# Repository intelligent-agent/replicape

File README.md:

:::python
     _____           __
    | ___ \         | (_)
    | |_/ /___ _ __ | |_  ___ __ _ _ __   ___
    |    // _ \  _ \| | |/ __/ _  |  _ \ / _ \
    | |\ \  __/ |_) | | | (_| (_| | |_) |  __/
    \_| \_\___| .__/|_|_|\___\__,_| .__/ \___|
             | |                 | |
             |_|                 |_|

Replicape is a 3D printer cape for BeagleBone.  

### Features: ###

* 5 stepper motors (Trinamic TMC2100) (X, Y, Z, E, H)  
* 3 high power MOSFETs (PWM controlled) for 2 extruders and 1 HPB.  (12..24V)  
* 4 medium power MOSFETs (PWM controlled) for up to 4 fans/LED strips.  (12V)  
* 3 analog input ports for thermistors. noise-filtered inputs and option for shielding  
* 6 inputs for end stops (X, Y, Z).  
* 1 bus for Dallas 1W temperature sensor for monitoring the cold end. Up to 10 sensors can be added to the bus.  
* 2 servo outputs.  
* 1 inductive sensor input.  
* Programmable current limits on steppers motor drivers (SMD). No need to manually adjust a pot meter.  
* Microstepping individually programmable for each SMD from 1 to 256.  
* All steppers are controlled by the Programmable Realtime Unit (PRU) for hard real time operation.  
* Compatible with [Manga Screen](https://bitbucket.org/intelligentagent/manga-screen)  
* Single 12 to 24V PSU, fans are still 12V.  
* Compatible with BeagleBone and BeagleBone Black (probably also green and blue).  
* Open source hardware and software. (CC BY-SA)  
* Software written in Python for maintainability and hackability.  
  
This is the repository for the hardware, the "firmware" (Redeem) has a [separate repository](https://bitbucket.org/intelligentagent/redeem)

### What is in here? ###

* This repository contains the files needed to reproduce the PCB and continue development.
* The latest revision is B3

### I want one! How much is it, and where can I get it? ###

It's $99 and you can [buy it in the store](http://www.thing-printer.com/product/replicape)

### I want to build my own board. How do I do that? ###

* Download the BOM and order the parts from Digi-key
* Send the GERBER files to a PCB manufacturer
* Get a reflow oven
* Populate the board

### I want a different version of this, who do I talk to? ###

Talk to Elias <elias at iagent dot no> 

### I have a Replicape, how do I wire it? ###
Look at the wiki page: [http://wiki.thing-printer.com](http://wiki.thing-printer.com)

### I want to read about the latest development of this board. Where can I do that? ###
The thing-prnter blog is a good place: [http://www.thing-printer.com/blog/](http://www.thing-printer.com/blog/)

### Who has contributed to this project? ###

* Elias Bakken
* Dirk Eichel
* Stoneshop
* Bent Furevik

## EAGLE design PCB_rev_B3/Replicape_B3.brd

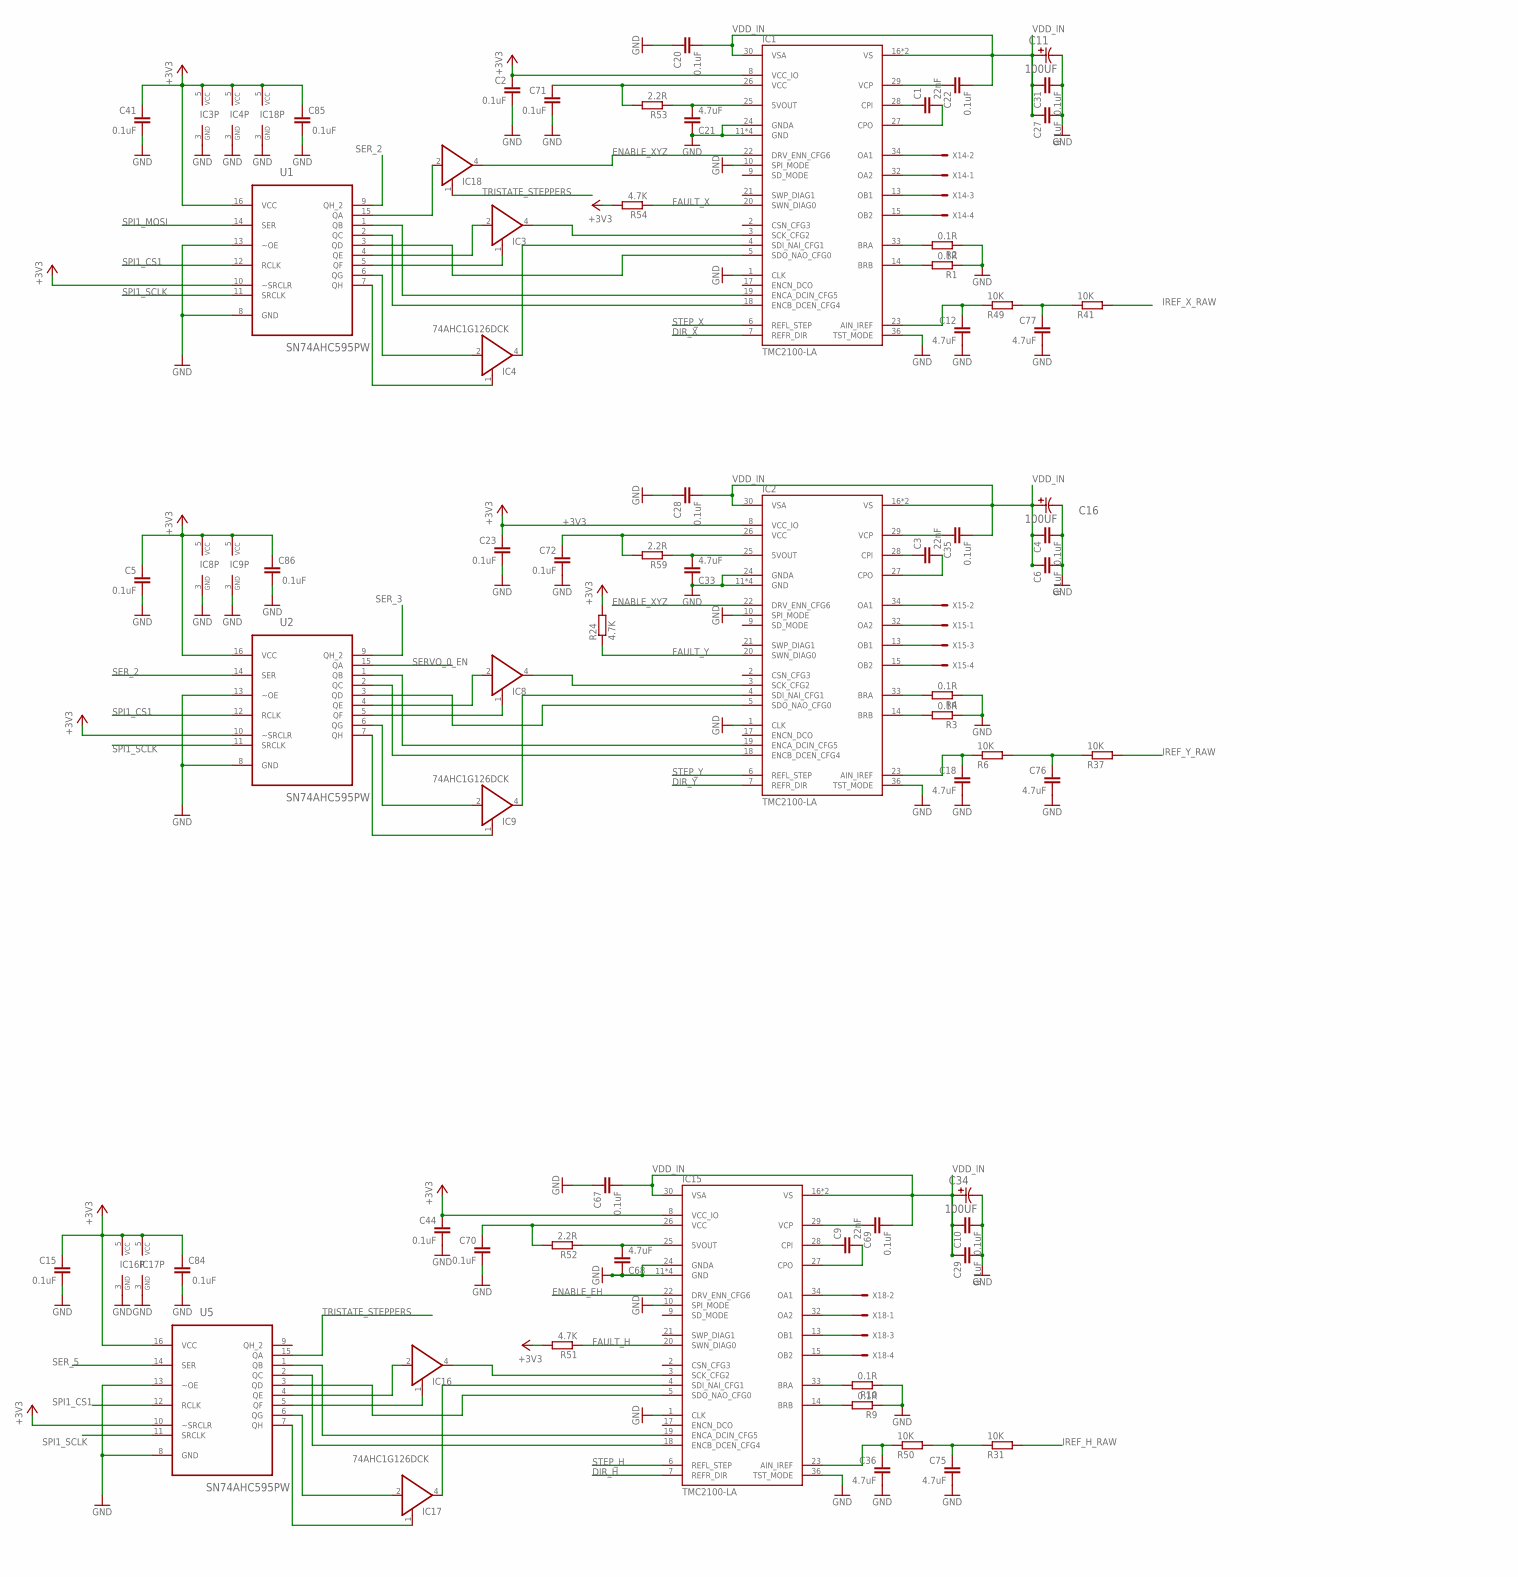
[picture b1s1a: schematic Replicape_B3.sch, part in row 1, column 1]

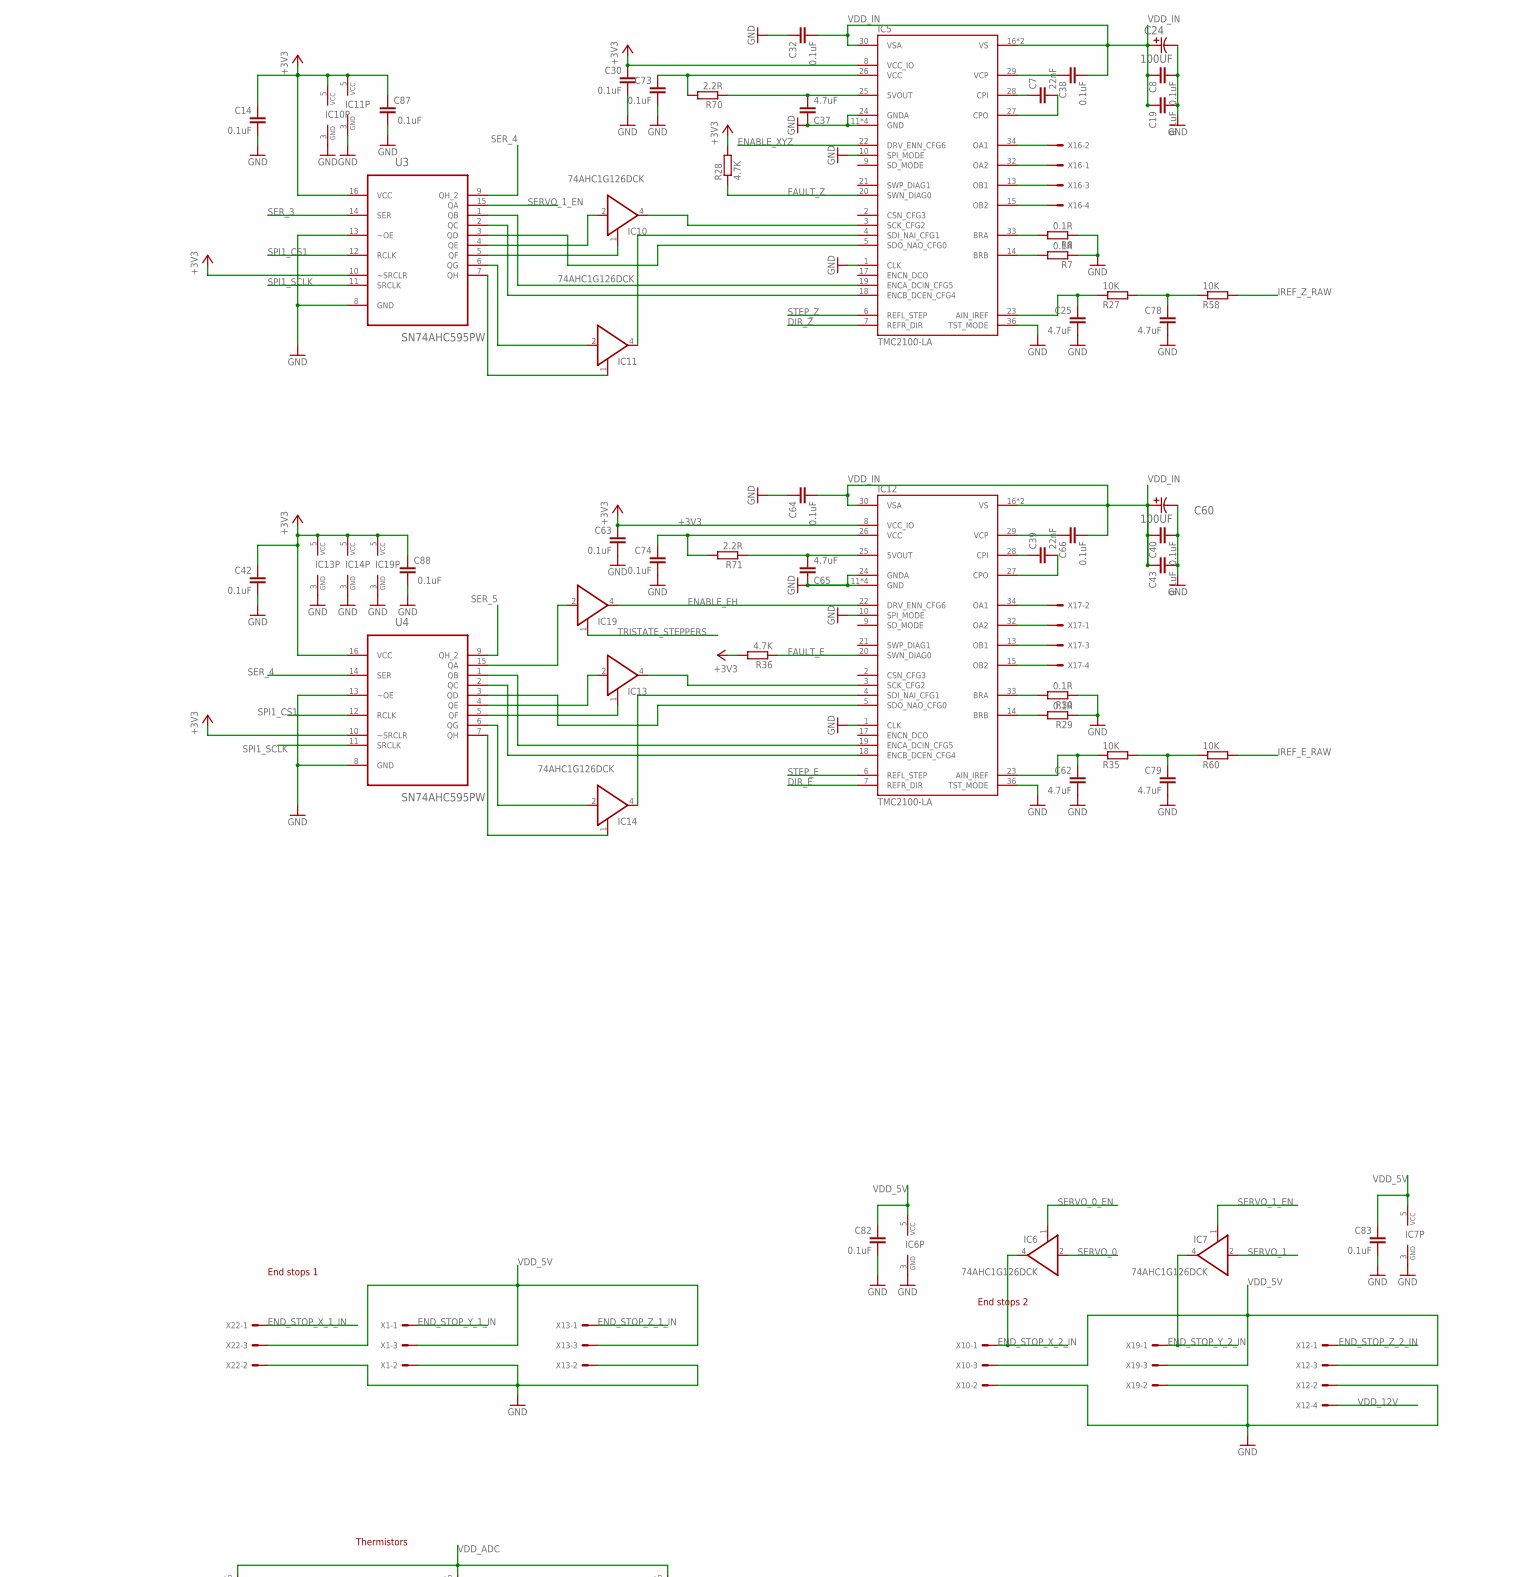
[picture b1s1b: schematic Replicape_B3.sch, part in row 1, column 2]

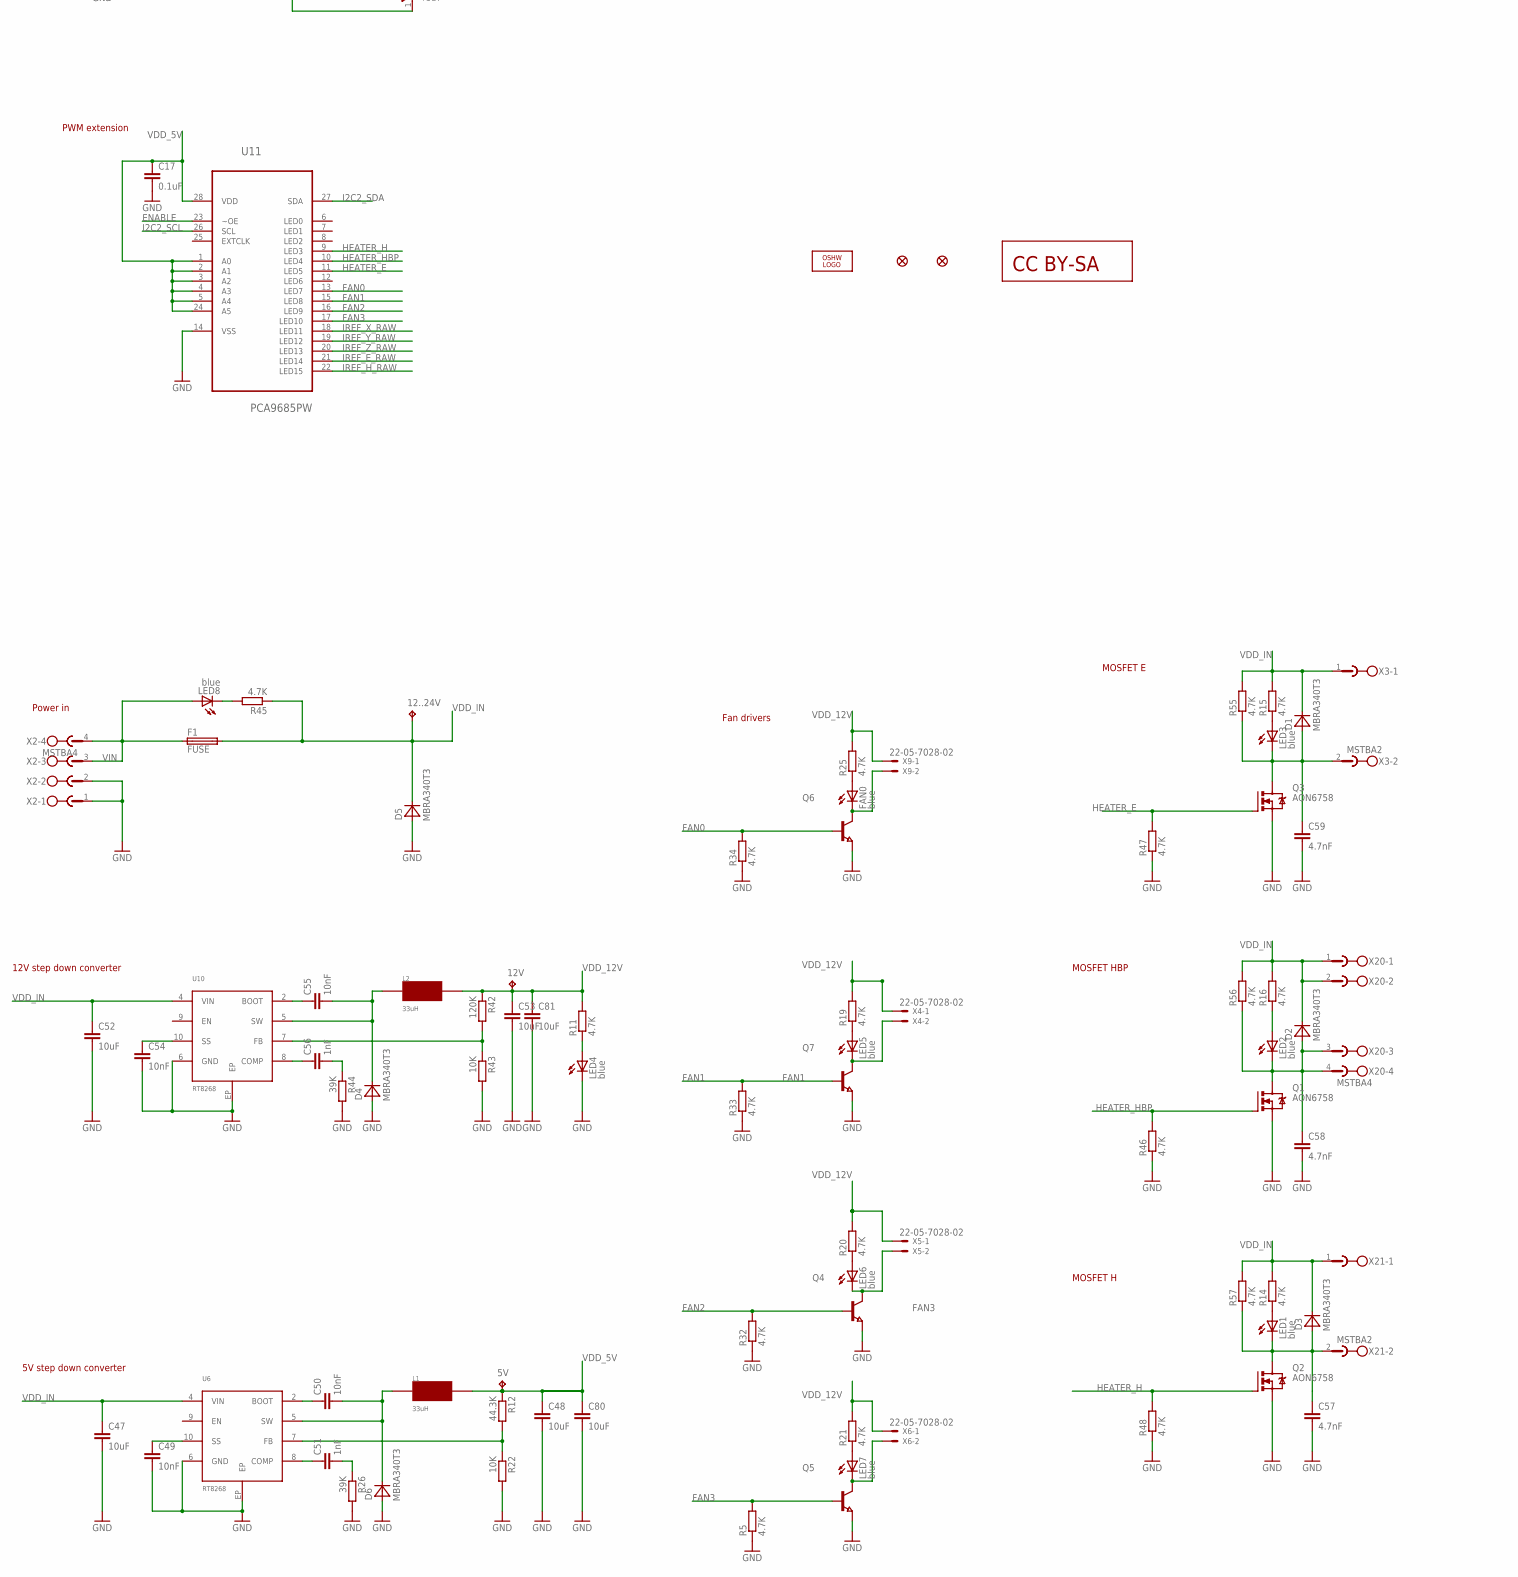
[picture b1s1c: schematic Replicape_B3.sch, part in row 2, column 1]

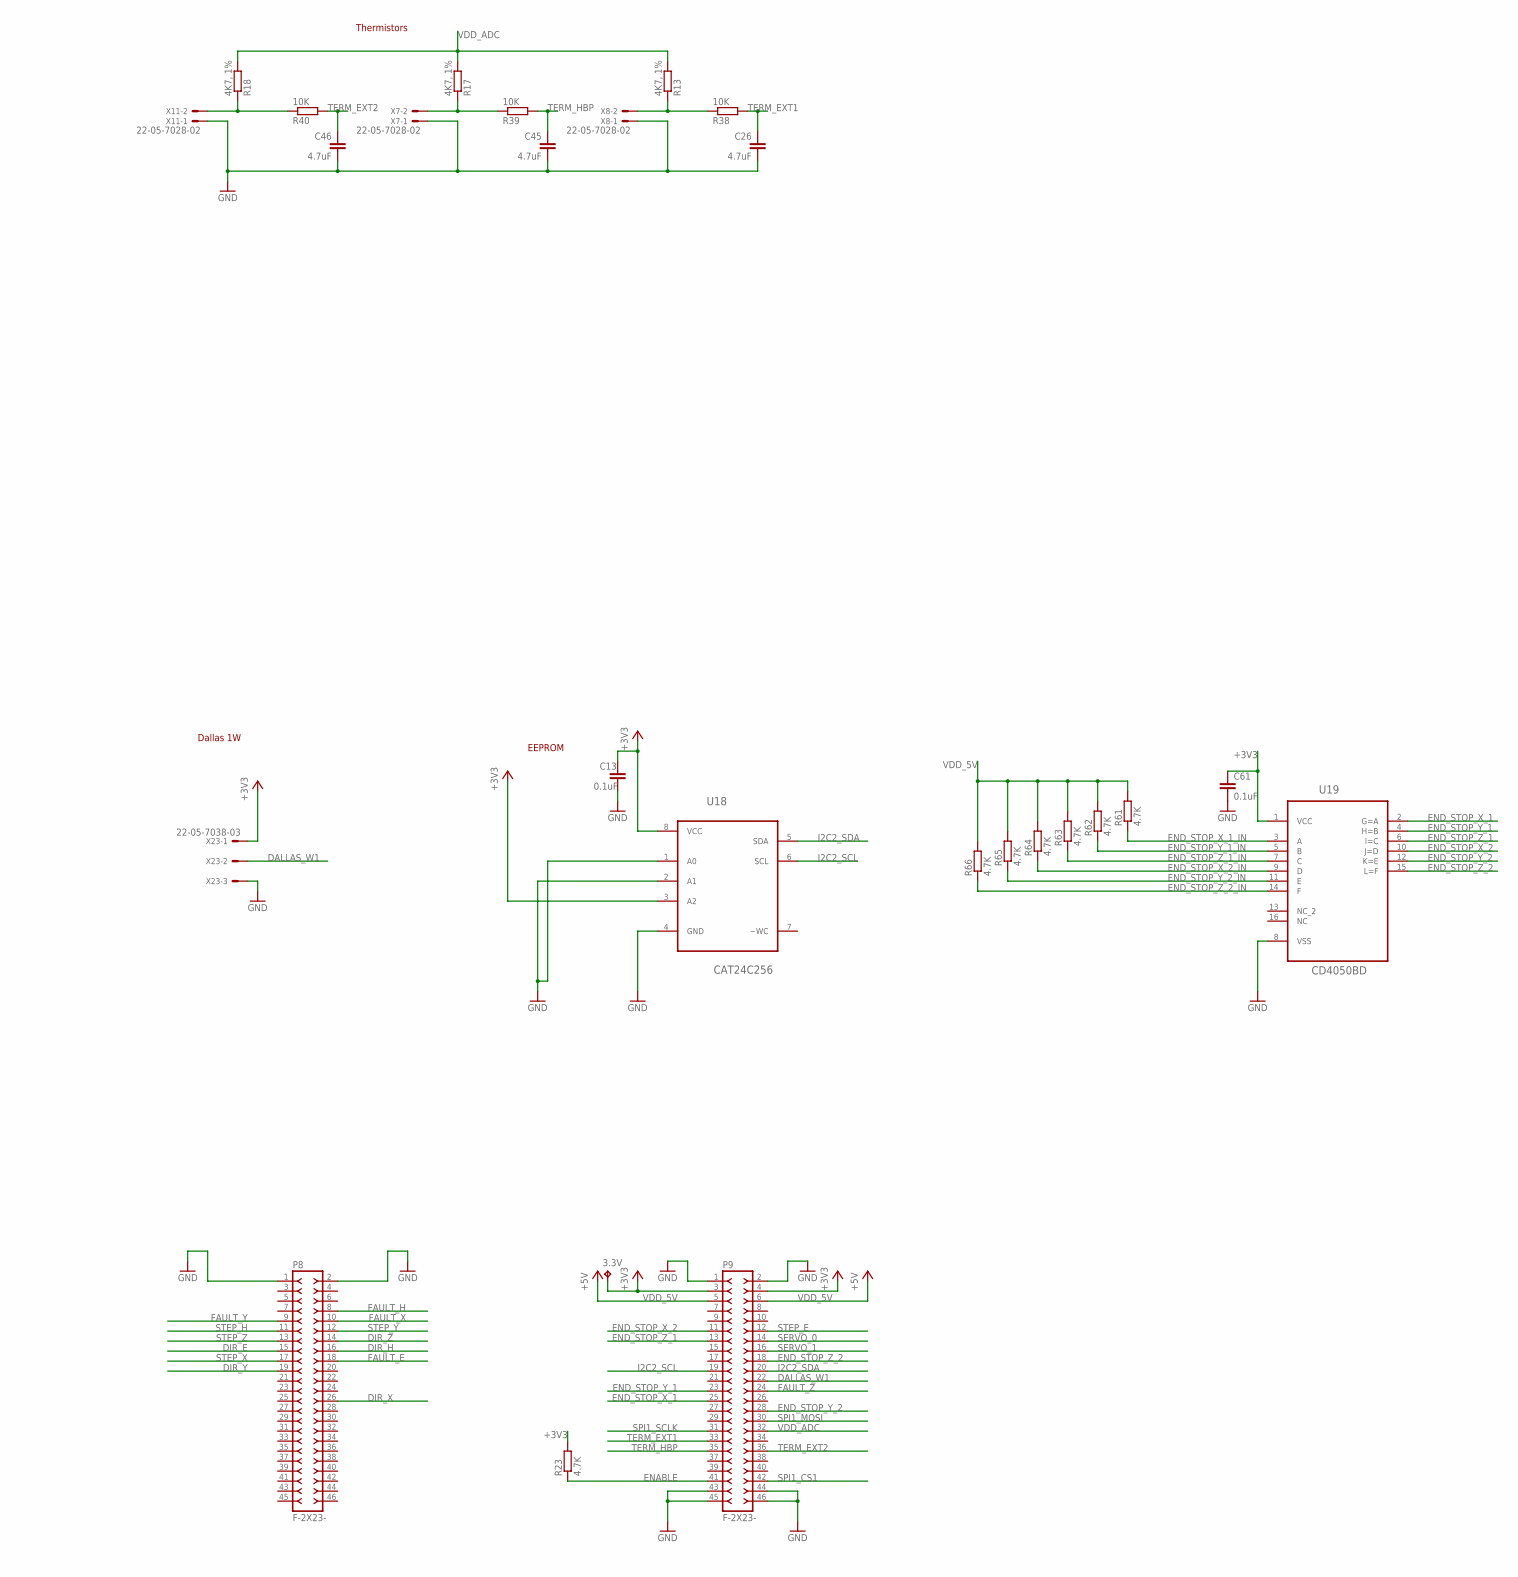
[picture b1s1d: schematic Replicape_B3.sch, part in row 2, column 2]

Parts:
3.3V, 5V, 12..24V, 12V: TPB1,27; B1,27
C1, C3, C7, C9, C39: 22nF; C0402
C2, C4, C5, C6, C8, C10, C13, C14, C15, C17, C19, C20, C22, C23, C27, C28, C29, C30, C31, C32, C35, C38, C40, C41, C42, C43, C44, C61, C63, C64, C66, C67, C69, C70, C71, C72, C73, C74, C82, C83, C84, C85, C86, C87, C88: 0.1uF; C0402
C11, C16, C24, C34, C60: 100UF; CAPAE660X800N
C12, C18, C21, C25, C26, C33, C36, C37, C45, C46, C62, C65, C68, C75, C76, C77, C78, C79: 4.7uF; C0402
C47, C48, C52, C53, C80, C81: 10uF; C1206
C49, C50, C54, C55: 10nF; C0402
C51, C56: 1nF; C0402
C57, C58, C59: 4.7nF; C0402
D1, D2, D3, D4, D5, D6: MBRA340T3; SMA
F1: FUSE; 3557
FAN0: blue; CHIP-LED0603
IC1, IC2, IC5, IC12, IC15: TMC2100-LA; QFN36-PAD
IC3, IC4, IC6, IC7, IC8, IC9, IC10, IC11, IC13, IC14, IC16, IC17, IC18, IC19: 74AHC1G126DCK; SC70-5
JP1, JP2: FIDUCIAL1X2.5; FIDUCIAL-1X2.5
L1, L2: 33uH; NR8040T330
LED1, LED2, LED3, LED4, LED5, LED6, LED7, LED8: blue; CHIP-LED0603
LOGO1: OSHW_LOGO_FILLX0200-NT; OSHW_FILLX200_NOTEXT
P8, P9: F-2X23-; DIL-100-2X23
Q1, Q2, Q3: AON6758; 8-DFN-EP-(5X6)
Q4, Q5, Q6, Q7: NPN-TRANSISTOR_SOT23; SOT23
R1, R2, R3, R4, R7, R8, R9, R10, R29, R30: 0.1R; R0805
R5, R11, R14, R15, R16, R19, R20, R21, R23, R24, R25, R28, R32, R33, R34, R36, R45, R46, R47, R48, R51, R54, R55, R56, R57, R61, R62, R63, R64, R65, R66: 4.7K; R0402
R6, R22, R27, R31, R35, R37, R38, R39, R40, R41, R43, R49, R50, R58, R60: 10K; R0402
R12: 44.3K; R0402
R13, R17, R18: 4K7, 1%; R0402
R26, R44: 39K; R0402
R42: 120K; R0402
R52, R53, R59, R70, R71: 2.2R; R0402
U1, U2, U3, U4, U5: SN74AHC595PW; SOP65P640X120-16N
U6, U10: RT8268; MSOP10
U11: PCA9685PW; SOP65P640X110-28N
U18: CAT24C256; SOIC127P600X175-8N
U19: CD4050BD; SOIC127P600X175-16N
U$4: CC-BY-SA
X1, X10, X13, X19, X22, X23: 22-05-7038-03; 7395-03
X2, X20: MSTBA4
X3, X21: MSTBA2
X4, X5, X6, X7, X8, X9, X11: 22-05-7028-02; 7395-02
X12, X14, X15, X16, X17, X18: 22-05-7048-04; 7395-04

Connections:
+3V3: 3.3V.TP, C2.1, C5.1, C13.1, C14.1, C15.1, C23.1, C30.1, C41.1, C42.1, C44.1, C61.1, C63.1, C84.1, C85.1, C86.1, C87.1, C88.1, IC1.8 (VCC_IO), IC2.8 (VCC_IO), IC3.5 (VCC), IC4.5 (VCC), IC5.8 (VCC_IO), IC8.5 (VCC), IC9.5 (VCC), IC10.5 (VCC), IC11.5 (VCC), IC12.8 (VCC_IO), IC13.5 (VCC), IC14.5 (VCC), IC15.8 (VCC_IO), IC16.5 (VCC), IC17.5 (VCC), IC18.5 (VCC), IC19.5 (VCC), P9.3, P9.4, R23.2, R24.2, R28.2, R36.2, R51.2, R54.2, U1.10 (~SRCLR), U1.16 (VCC), U2.10 (~SRCLR), U2.16 (VCC), U3.10 (~SRCLR), U3.16 (VCC), U4.10 (~SRCLR), U4.16 (VCC), U5.10 (~SRCLR), U5.16 (VCC), U18.3 (A2), U18.8 (VCC), U19.1 (VCC), X23.1
DALLAS_W1: P9.22, X23.2
DIR_E: IC12.7 (REFR_DIR), P8.15
DIR_H: IC15.7 (REFR_DIR), P8.16
DIR_X: IC1.7 (REFR_DIR), P8.26
DIR_Y: IC2.7 (REFR_DIR), P8.19
DIR_Z: IC5.7 (REFR_DIR), P8.14
ENABLE: P9.41, R23.1, U11.23 (~OE)
ENABLE_EH: IC12.22 (DRV_ENN_CFG6), IC15.22 (DRV_ENN_CFG6), IC19.4 (O)
ENABLE_XYZ: IC1.22 (DRV_ENN_CFG6), IC2.22 (DRV_ENN_CFG6), IC5.22 (DRV_ENN_CFG6), IC18.4 (O)
END_STOP_X_1: P9.25, U19.2 (G=A)
END_STOP_X_1_IN: R61.1, U19.3 (A), X22.1
END_STOP_X_2: P9.11, U19.10 (J=D)
END_STOP_X_2_IN: IC6.4 (O), R64.1, U19.9 (D), X10.1
END_STOP_Y_1: P9.23, U19.4 (H=B)
END_STOP_Y_1_IN: R62.1, U19.5 (B), X1.1
END_STOP_Y_2: P9.28, U19.12 (K=E)
END_STOP_Y_2_IN: IC7.4 (O), R65.1, U19.11 (E), X19.1
END_STOP_Z_1: P9.13, U19.6 (I=C)
END_STOP_Z_1_IN: R63.1, U19.7 (C), X13.1
END_STOP_Z_2: P9.18, U19.15 (L=F)
END_STOP_Z_2_IN: R66.1, U19.14 (F), X12.1
FAN0: Q6.1 (B), R34.2, U11.13 (LED7)
FAN1: Q7.1 (B), R33.2, U11.15 (LED8)
FAN2: Q4.1 (B), R32.2, U11.16 (LED9)
FAN3: Q5.1 (B), R5.2, U11.17 (LED10)
FAULT_E: IC12.20 (SWN_DIAG0), P8.18, R36.1
FAULT_H: IC15.20 (SWN_DIAG0), P8.8, R51.1
FAULT_X: IC1.20 (SWN_DIAG0), P8.10, R54.1
FAULT_Y: IC2.20 (SWN_DIAG0), P8.9, R24.1
FAULT_Z: IC5.20 (SWN_DIAG0), P9.24, R28.1
GND: C2.2, C4.2, C5.2, C6.2, C8.2, C10.2, C11.2, C12.2, C13.2, C14.2, C15.2, C16.2, C17.2, C18.2, C19.2, C20.1, C21.1, C23.2, C24.2, C25.2, C26.2, C27.2, C28.1, C29.2, C30.2, C31.2, C32.1, C33.1, C34.2, C36.2, C37.1, C40.2, C41.2, C42.2, C43.2, C44.2, C45.2, C46.2, C47.2, C48.2, C49.2, C52.2, C53.2, C54.2, C57.2, C58.2, C59.2, C60.2, C61.2, C62.2, C63.2, C64.1, C65.1, C67.1, C68.1, C70.2, C71.2, C72.2, C73.2, C74.2, C75.2, C76.2, C77.2, C78.2, C79.2, C80.2, C81.2, C82.2, C83.2, C84.2, C85.2, C86.2, C87.2, C88.2, D4.A, D5.A, D6.A, IC1.1 (CLK), IC1.10 (SPI_MODE), IC1.11 (GND), IC1.12 (GND), IC1.24 (GNDA), IC1.35 (GND), IC1.36 (TST_MODE), IC1.TP (GND), IC2.1 (CLK), IC2.10 (SPI_MODE), IC2.11 (GND), IC2.12 (GND), IC2.24 (GNDA), IC2.35 (GND), IC2.36 (TST_MODE), IC2.TP (GND), IC3.3 (GND), IC4.3 (GND), IC5.1 (CLK), IC5.10 (SPI_MODE), IC5.11 (GND), IC5.12 (GND), IC5.24 (GNDA), IC5.35 (GND), IC5.36 (TST_MODE), IC5.TP (GND), IC6.3 (GND), IC7.3 (GND), IC8.3 (GND), IC9.3 (GND), IC10.3 (GND), IC11.3 (GND), IC12.1 (CLK), IC12.10 (SPI_MODE), IC12.11 (GND), IC12.12 (GND), IC12.24 (GNDA), IC12.35 (GND), IC12.36 (TST_MODE), IC12.TP (GND), IC13.3 (GND), IC14.3 (GND), IC15.1 (CLK), IC15.10 (SPI_MODE), IC15.11 (GND), IC15.12 (GND), IC15.24 (GNDA), IC15.35 (GND), IC15.36 (TST_MODE), IC15.TP (GND), IC16.3 (GND), IC17.3 (GND), IC18.3 (GND), IC19.3 (GND), LED4.C, P8.1, P8.2, P9.1, P9.2, P9.43, P9.44, P9.45, P9.46, Q1.1 (S), Q1.2 (S), Q1.3 (S), Q2.1 (S), Q2.2 (S), Q2.3 (S), Q3.1 (S), Q3.2 (S), Q3.3 (S), Q4.2 (E), Q5.2 (E), Q6.2 (E), Q7.2 (E), R1.1, R2.1, R3.1, R4.1, R5.1, R7.1, R8.1, R9.1, R10.1, R22.2, R26.2, R29.1, R30.1, R32.1, R33.1, R34.1, R43.2, R44.2, R46.1, R47.1, R48.1, U1.8 (GND), U1.13 (~OE), U2.8 (GND), U2.13 (~OE), U3.8 (GND), U3.13 (~OE), U4.8 (GND), U4.13 (~OE), U5.8 (GND), U5.13 (~OE), U6.6 (GND), U6.EP, U10.6 (GND), U10.EP, U11.14 (VSS), U18.1 (A0), U18.2 (A1), U18.4 (GND), U19.8 (VSS), X1.2, X2.1, X2.2, X7.1, X8.1, X10.2, X11.1, X12.2, X13.2, X19.2, X22.2, X23.3
HEATER_E: Q3.4 (G), R47.2, U11.11 (LED5)
HEATER_H: Q2.4 (G), R48.2, U11.9 (LED3)
HEATER_HBP: Q1.4 (G), R46.2, U11.10 (LED4)
I2C2_SCL: P9.19, U11.26 (SCL), U18.6 (SCL)
I2C2_SDA: P9.20, U11.27 (SDA), U18.5 (SDA)
IREF_E: C79.1, R35.2, R60.1
IREF_E_RAW: R60.2, U11.21 (LED14)
IREF_H: C75.1, R31.1, R50.2
IREF_H_RAW: R31.2, U11.22 (LED15)
IREF_X: C77.1, R41.1, R49.2
IREF_X_RAW: R41.2, U11.18 (LED11)
IREF_Y: C76.1, R6.2, R37.1
IREF_Y_RAW: R37.2, U11.19 (LED12)
IREF_Z: C78.1, R27.2, R58.1
IREF_Z_RAW: R58.2, U11.20 (LED13)
unnamed: IC2.13 (OB1), X15.3
unnamed: C3.2, IC2.27 (CPO)
unnamed: IC4.1 (OE), U1.7 (QH)
unnamed: IC4.2 (I), U1.6 (QG)
unnamed: IC1.18 (ENCB_DCEN_CFG4), U1.2 (QC)
unnamed: LED8.C, R45.2
unnamed: LED5.A, R19.1
unnamed: FAN0.C, Q6.3 (C), X9.2
unnamed: C9.2, IC15.27 (CPO)
unnamed: IC15.14 (BRB), R9.2
unnamed: C7.2, IC5.27 (CPO)
unnamed: IC5.14 (BRB), R7.2
unnamed: C1.1, IC1.28 (CPI)
unnamed: C1.2, IC1.27 (CPO)
unnamed: IC1.14 (BRB), R1.2
unnamed: IC1.33 (BRA), R2.2
unnamed: C12.1, IC1.23 (AIN_IREF), R49.1
unnamed: FAN0.A, R25.1
unnamed: IC2.32 (OA2), X15.1
unnamed: R12.2, R22.1, U6.7 (FB)
unnamed: IC5.33 (BRA), R8.2
unnamed: C50.2, D6.C, L1.P$2, U6.5 (SW)
unnamed: C25.1, IC5.23 (AIN_IREF), R27.1
unnamed: C7.1, IC5.28 (CPI)
unnamed: IC5.3 (SCK_CFG2), IC10.4 (O)
unnamed: IC5.15 (OB2), X16.4
unnamed: IC15.33 (BRA), R10.2
unnamed: C21.2, IC1.25 (5VOUT), R53.1
unnamed: IC5.32 (OA2), X16.1
unnamed: C22.1, IC1.29 (VCP)
unnamed: IC3.2 (I), U1.4 (QE)
unnamed: IC2.14 (BRB), R3.2
unnamed: IC2.33 (BRA), R4.2
unnamed: IC5.13 (OB1), X16.3
unnamed: C18.1, IC2.23 (AIN_IREF), R6.1
unnamed: IC12.13 (OB1), X17.3
unnamed: IC3.1 (OE), U1.5 (QF)
unnamed: C3.1, IC2.28 (CPI)
unnamed: IC2.3 (SCK_CFG2), IC8.4 (O)
unnamed: IC1.19 (ENCA_DCIN_CFG5), U1.1 (QB)
unnamed: IC1.5 (SDO_NAO_CFG0), U1.3 (QD)
unnamed: IC2.15 (OB2), X15.4
unnamed: IC2.34 (OA1), X15.2
unnamed: C33.2, IC2.25 (5VOUT), R59.1
unnamed: C35.1, IC2.29 (VCP)
unnamed: IC2.4 (SDI_NAI_CFG1), IC9.4 (O)
unnamed: IC5.34 (OA1), X16.2
unnamed: C37.2, IC5.25 (5VOUT), R70.1
unnamed: C38.1, IC5.29 (VCP)
unnamed: IC2.5 (SDO_NAO_CFG0), U2.3 (QD)
unnamed: IC5.4 (SDI_NAI_CFG1), IC11.4 (O)
unnamed: IC5.5 (SDO_NAO_CFG0), U3.3 (QD)
unnamed: IC2.18 (ENCB_DCEN_CFG4), U2.2 (QC)
unnamed: IC5.18 (ENCB_DCEN_CFG4), U3.2 (QC)
unnamed: IC5.19 (ENCA_DCIN_CFG5), U3.1 (QB)
unnamed: IC11.1 (OE), U3.7 (QH)
unnamed: C49.1, U6.10 (SS)
unnamed: IC11.2 (I), U3.6 (QG)
unnamed: IC10.1 (OE), U3.5 (QF)
unnamed: IC10.2 (I), U3.4 (QE)
unnamed: C57.1, D3.A, LED1.C, Q2.5 (D), Q2.6 (D), Q2.7 (D), Q2.8 (D), Q2.TH (D), R57.1, X21.2
unnamed: IC2.19 (ENCA_DCIN_CFG5), U2.1 (QB)
unnamed: IC9.1 (OE), U2.7 (QH)
unnamed: IC9.2 (I), U2.6 (QG)
unnamed: IC8.1 (OE), U2.5 (QF)
unnamed: IC8.2 (I), U2.4 (QE)
unnamed: C39.2, IC12.27 (CPO)
unnamed: IC12.14 (BRB), R29.2
unnamed: IC12.33 (BRA), R30.2
unnamed: C50.1, U6.2 (BOOT)
unnamed: C62.1, IC12.23 (AIN_IREF), R35.1
unnamed: C39.1, IC12.28 (CPI)
unnamed: IC12.3 (SCK_CFG2), IC13.4 (O)
unnamed: IC12.15 (OB2), X17.4
unnamed: IC12.34 (OA1), X17.2
unnamed: C65.2, IC12.25 (5VOUT), R71.1
unnamed: C66.1, IC12.29 (VCP)
unnamed: IC12.4 (SDI_NAI_CFG1), IC14.4 (O)
unnamed: IC12.5 (SDO_NAO_CFG0), U4.3 (QD)
unnamed: IC12.18 (ENCB_DCEN_CFG4), U4.2 (QC)
unnamed: IC12.19 (ENCA_DCIN_CFG5), U4.1 (QB)
unnamed: IC14.1 (OE), U4.7 (QH)
unnamed: IC14.2 (I), U4.6 (QG)
unnamed: IC13.1 (OE), U4.5 (QF)
unnamed: C51.1, U6.8 (COMP)
unnamed: C36.1, IC15.23 (AIN_IREF), R50.1
unnamed: C9.1, IC15.28 (CPI)
unnamed: IC15.3 (SCK_CFG2), IC16.4 (O)
unnamed: IC15.15 (OB2), X18.4
unnamed: IC13.2 (I), U4.4 (QE)
unnamed: IC15.34 (OA1), X18.2
unnamed: C68.2, IC15.25 (5VOUT), R52.1
unnamed: LED4.A, R11.1
unnamed: C51.2, R26.1
unnamed: C69.1, IC15.29 (VCP)
unnamed: IC15.4 (SDI_NAI_CFG1), IC17.4 (O)
unnamed: IC15.5 (SDO_NAO_CFG0), U5.3 (QD)
unnamed: IC15.18 (ENCB_DCEN_CFG4), U5.2 (QC)
unnamed: IC15.19 (ENCA_DCIN_CFG5), U5.1 (QB)
unnamed: IC17.1 (OE), U5.7 (QH)
unnamed: IC17.2 (I), U5.6 (QG)
unnamed: IC16.1 (OE), U5.5 (QF)
unnamed: IC16.2 (I), U5.4 (QE)
unnamed: C70.1, IC15.26 (VCC), R52.2
unnamed: C71.1, IC1.26 (VCC), R53.2
unnamed: C73.1, IC5.26 (VCC), R70.2
unnamed: C72.1, IC2.26 (VCC), R59.2
unnamed: C74.1, IC12.26 (VCC), R71.2
unnamed: IC12.32 (OA2), X17.1
unnamed: IC15.13 (OB1), X18.3
unnamed: LED7.C, Q5.3 (C), X6.2
unnamed: LED6.C, Q4.3 (C), X5.2
unnamed: LED5.C, Q7.3 (C), X4.2
unnamed: LED6.A, R20.1
unnamed: LED7.A, R21.1
unnamed: IC15.32 (OA2), X18.1
unnamed: IC18.2 (I), U1.15 (QA)
unnamed: IC19.2 (I), U4.15 (QA)
unnamed: LED3.A, R15.1
unnamed: LED1.A, R14.1
unnamed: LED2.A, R16.1
unnamed: R42.2, R43.1, U10.7 (FB)
unnamed: C59.1, D1.A, LED3.C, Q3.5 (D), Q3.6 (D), Q3.7 (D), Q3.8 (D), Q3.TH (D), R55.1, X3.2
unnamed: R13.1, R38.1, X8.2
unnamed: C55.2, D4.C, L2.P$2, U10.5 (SW)
unnamed: R18.1, R40.1, X11.2
unnamed: R17.1, R39.1, X7.2
unnamed: C58.1, D2.A, LED2.C, Q1.5 (D), Q1.6 (D), Q1.7 (D), Q1.8 (D), Q1.TH (D), R56.1, X20.3, X20.4
unnamed: C54.1, U10.10 (SS)
unnamed: C56.1, U10.8 (COMP)
unnamed: C55.1, U10.2 (BOOT)
unnamed: C56.2, R44.1
SERVO_0: IC6.2 (I), P9.14
SERVO_0_EN: IC6.1 (OE), U2.15 (QA)
SERVO_1: IC7.2 (I), P9.16
SERVO_1_EN: IC7.1 (OE), U3.15 (QA)
SER_2: U1.9 (QH_2), U2.14 (SER)
SER_3: U2.9 (QH_2), U3.14 (SER)
SER_4: U3.9 (QH_2), U4.14 (SER)
SER_5: U4.9 (QH_2), U5.14 (SER)
SPI1_CS1: P9.42, U1.12 (RCLK), U2.12 (RCLK), U3.12 (RCLK), U4.12 (RCLK), U5.12 (RCLK)
SPI1_MOSI: P9.30, U1.14 (SER)
SPI1_SCLK: P9.31, U1.11 (SRCLK), U2.11 (SRCLK), U3.11 (SRCLK), U4.11 (SRCLK), U5.11 (SRCLK)
STEP_E: IC12.6 (REFL_STEP), P9.12
STEP_H: IC15.6 (REFL_STEP), P8.11
STEP_X: IC1.6 (REFL_STEP), P8.17
STEP_Y: IC2.6 (REFL_STEP), P8.12
STEP_Z: IC5.6 (REFL_STEP), P8.13
TERM_EXT1: C26.1, P9.33, R38.2
TERM_EXT2: C46.1, P9.36, R40.2
TERM_HBP: C45.1, P9.35, R39.2
TRISTATE_STEPPERS: IC18.1 (OE), IC19.1 (OE), U5.15 (QA)
VDD_5V: 5V.TP, C17.1, C48.1, C80.1, C82.1, C83.1, IC6.5 (VCC), IC7.5 (VCC), L1.P$1, P9.5, P9.6, R12.1, R61.2, R62.2, R63.2, R64.2, R65.2, R66.2, U11.1 (A0), U11.2 (A1), U11.3 (A2), U11.4 (A3), U11.5 (A4), U11.24 (A5), U11.28 (VDD), X1.3, X10.3, X12.3, X13.3, X19.3, X22.3
VDD_12V: 12V.TP, C53.1, C81.1, L2.P$1, R11.2, R19.2, R20.2, R21.2, R25.2, R42.1, X4.1, X5.1, X6.1, X9.1, X12.4
VDD_ADC: P9.32, R13.2, R17.2, R18.2
VDD_IN: 12..24V.TP, C4.1, C6.1, C8.1, C10.1, C11.1, C16.1, C19.1, C20.2, C22.2, C24.1, C27.1, C28.2, C29.1, C31.1, C32.2, C34.1, C35.2, C38.2, C40.1, C43.1, C47.1, C52.1, C60.1, C64.2, C66.2, C67.2, C69.2, D1.C, D2.C, D3.C, D5.C, F1.P$3 (2), F1.P$4 (2), IC1.16 (VS), IC1.30 (VSA), IC1.31 (VS), IC2.16 (VS), IC2.30 (VSA), IC2.31 (VS), IC5.16 (VS), IC5.30 (VSA), IC5.31 (VS), IC12.16 (VS), IC12.30 (VSA), IC12.31 (VS), IC15.16 (VS), IC15.30 (VSA), IC15.31 (VS), R14.2, R15.2, R16.2, R45.1, R55.2, R56.2, R57.2, U6.4 (VIN), U10.4 (VIN), X3.1, X20.1, X20.2, X21.1
VIN: F1.P$1 (1), F1.P$2 (1), LED8.A, X2.3, X2.4
X_A1: IC1.34 (OA1), X14.2
X_A2: IC1.32 (OA2), X14.1
X_B1: IC1.13 (OB1), X14.3
X_B2: IC1.15 (OB2), X14.4
X_CFG1: IC1.4 (SDI_NAI_CFG1), IC4.4 (O)
X_CFG2: IC1.3 (SCK_CFG2), IC3.4 (O)

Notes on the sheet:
Fan drivers
PWM extension
Power in
5V step down converter
12V step down converter
MOSFET E
MOSFET HBP
MOSFET H
End stops 2
Thermistors
End stops 1
EEPROM
Dallas 1W

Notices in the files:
parts and their libraries:
con-headers-jp: Copyright (C) 2008, Bob Starr
